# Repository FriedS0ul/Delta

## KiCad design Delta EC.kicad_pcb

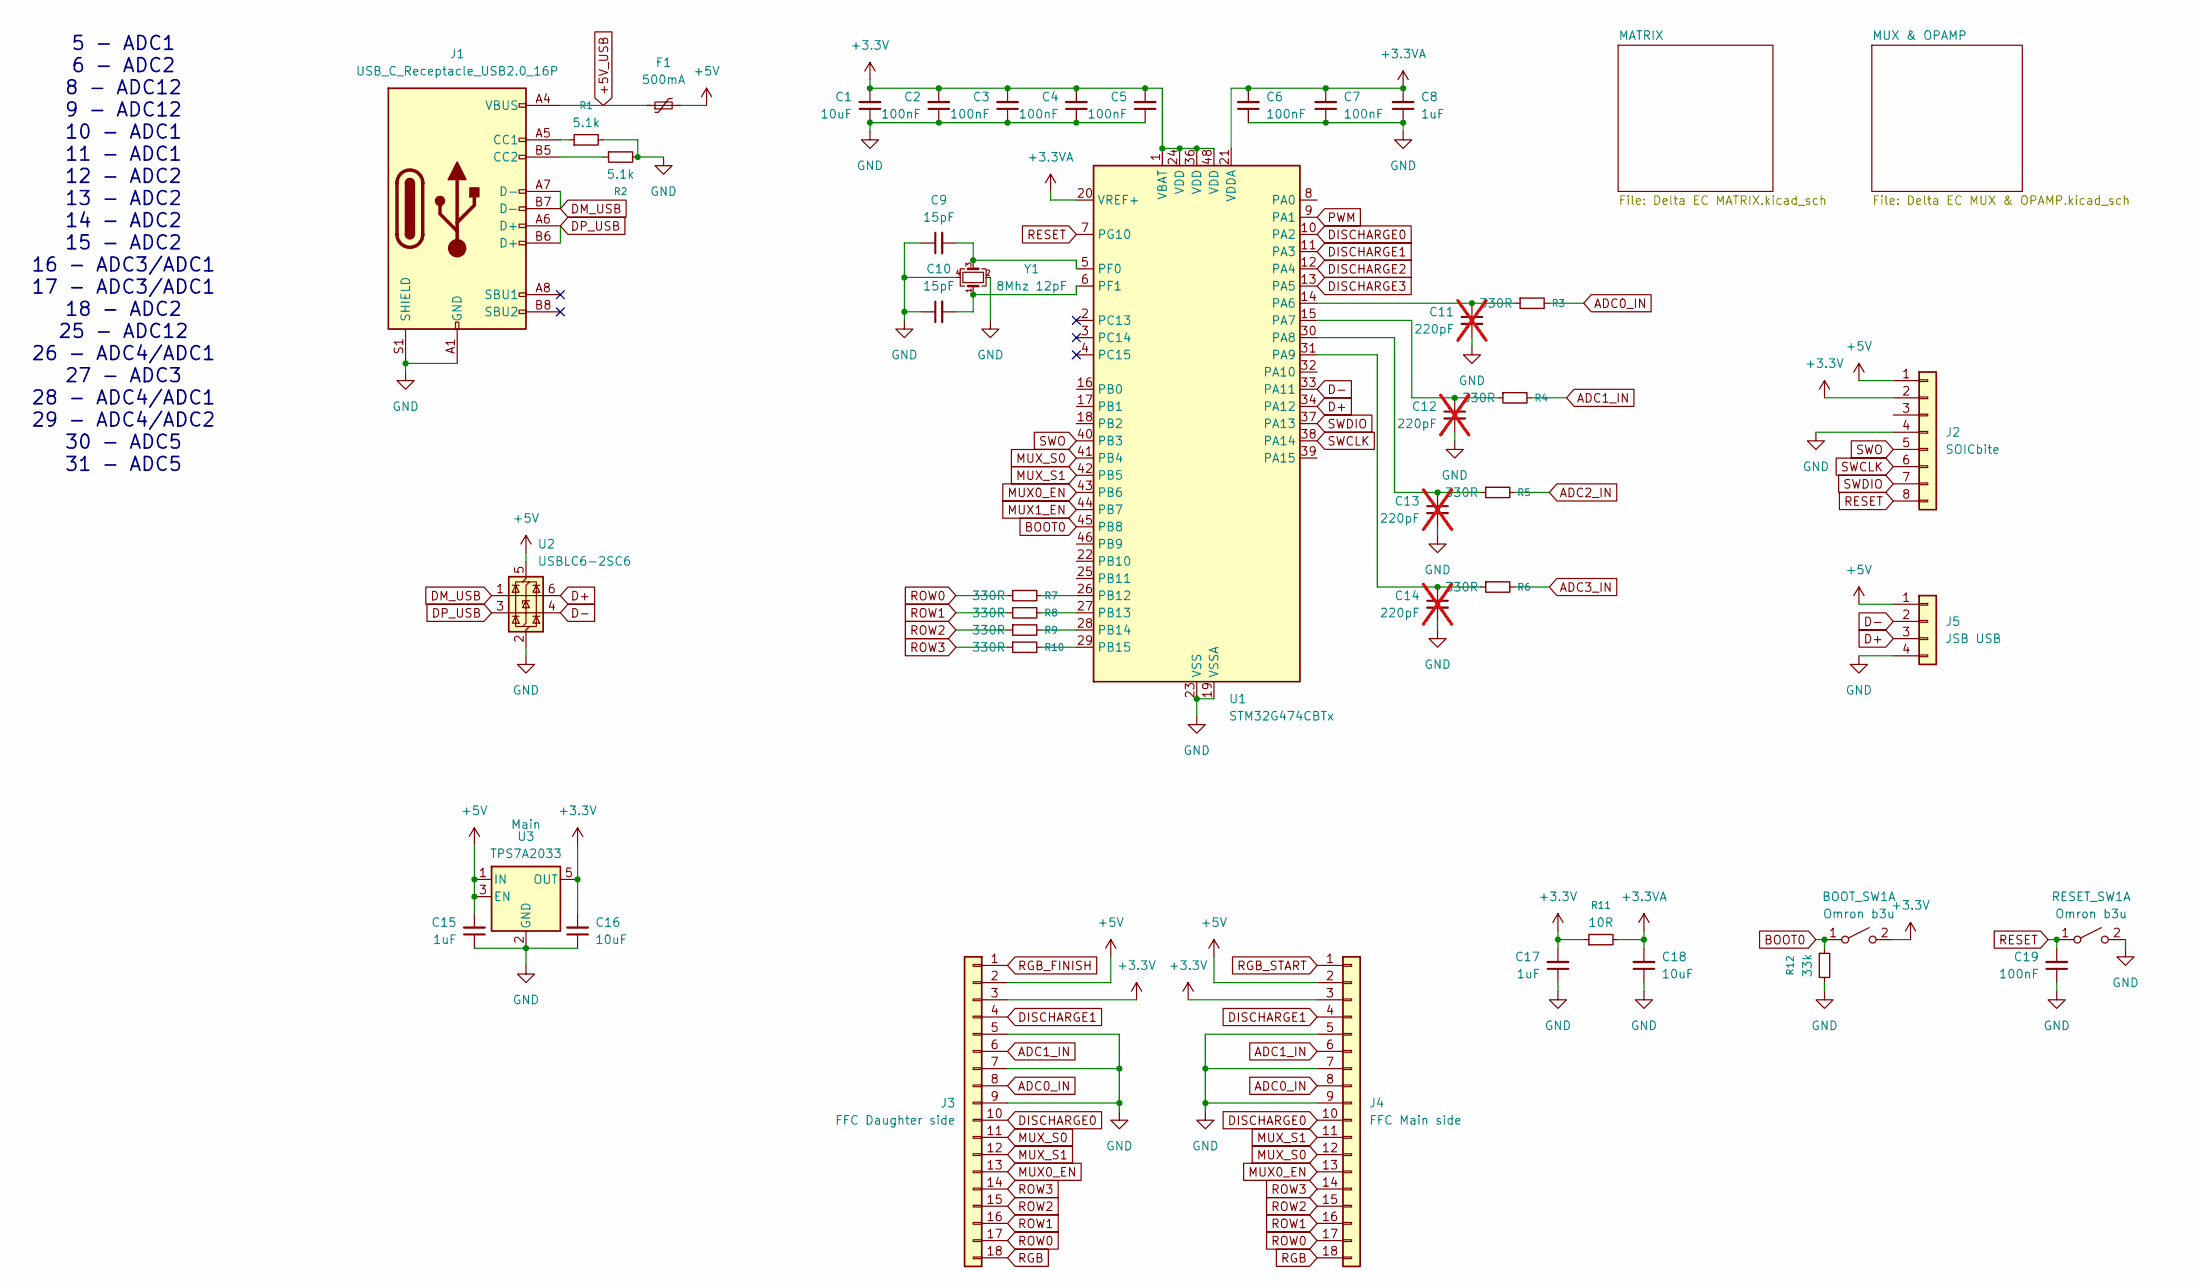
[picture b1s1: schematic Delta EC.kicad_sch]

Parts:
BOOT_SW1: Omron b3u; SW_SPST_B3U-1000P
C1, C16, C18: 10uF; C_0805_2012Metric
C2, C3, C4, C5, C6, C7, C19: 100nF; C_0402_1005Metric
C8, C15, C17: 1uF; C_0603_1608Metric
C9, C10: 15pF; C_0402_1005Metric
C11, C12, C13, C14: 220pF; C_0603_1608Metric; not fitted
F1: 500mA; Fuse_1206_3216Metric
J1: USB_C_Receptacle_USB2.0_16P; USB_C_Receptacle_GCT_USB4105-xx-A_16P_TopMnt_Horizontal
J2: SOICbite; SOICbite_footprint
J3: FFC Daughter side; TE_1-1734839-8_1x18-1MP_P0.5mm_Horizontal
J4: FFC Main side; TE_1-1734839-8_1x18-1MP_P0.5mm_Horizontal
J5: JSB USB; JST_SH_SM04B-SRSS-TB_1x04-1MP_P1.00mm_Horizontal
R1, R2: 5.1k; R_0603_1608Metric
R3, R4, R5, R6, R7, R8, R9, R10: 330R; R_0603_1608Metric
R11: 10R; R_0603_1608Metric
R12: 33k; R_0603_1608Metric
RESET_SW1: Omron b3u; SW_SPST_B3U-1000P
U1: STM32G474CBTx; LQFP-48_7x7mm_P0.5mm
U2: USBLC6-2SC6; SOT-23-6
U3: TPS7A2033; SOT-23-5
Y1: 8Mhz 12pF; Crystal_SMD_3225-4Pin_3.2x2.5mm

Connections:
+3.3V: BOOT_SW1.2 (B), C1.2, C2.2, C3.2, C4.2, C5.2, C16.2, C17.2, J2.2, J3.3, J4.3, R11.1, U1.1 (VBAT), U1.24 (VDD), U1.36 (VDD), U1.48 (VDD), U3.5 (OUT)
+3.3VA: C6.2, C7.2, C8.2, C18.2, R11.2, U1.20 (VREF+), U1.21 (VDDA); also elsewhere on the board
+5V: C15.2, F1.2, J2.1, J3.2, J4.2, J5.1, U2.5 (VBUS), U3.1 (IN), U3.3 (EN); also elsewhere on the board
+5V_USB: F1.1, J1.A4 (VBUS), J1.A9 (VBUS), J1.B4 (VBUS), J1.B9 (VBUS)
ADC0_IN: J3.8, J4.8, R3.2; also elsewhere on the board
ADC1_IN: J3.6, J4.6, R4.2; also elsewhere on the board
ADC2_IN: R5.2; also elsewhere on the board
ADC3_IN: R6.2; also elsewhere on the board
BOOT0: BOOT_SW1.1 (A), R12.1, U1.45 (PB8)
D+: J5.3, U1.34 (PA12), U2.6 (I/O1)
D-: J5.2, U1.33 (PA11), U2.4 (I/O2)
DISCHARGE0: J3.10, J4.10, U1.10 (PA2); also elsewhere on the board
DISCHARGE1: J3.4, J4.4, U1.11 (PA3); also elsewhere on the board
DISCHARGE2: U1.12 (PA4); also elsewhere on the board
DISCHARGE3: U1.13 (PA5); also elsewhere on the board
DM_USB: J1.A7 (D-), J1.B7 (D-), U2.1 (I/O1)
DP_USB: J1.A6 (D+), J1.B6 (D+), U2.3 (I/O2)
GND: C1.1, C2.1, C3.1, C4.1, C5.1, C6.1, C7.1, C8.1, C9.1, C10.1, C11.2, C12.2, C13.2, C14.2, C15.1, C16.1, C17.1, C18.1, C19.1, J1.A1 (GND), J1.A12 (GND), J1.B1 (GND), J1.B12 (GND), J1.S1 (SHIELD), J2.4, J3.5, J3.7, J3.9, J4.5, J4.7, J4.9, J5.4, R1.2, R2.2, R12.2, RESET_SW1.2 (B), U1.19 (VSSA), U1.23 (VSS), U1.35 (VSS), U1.47 (VSS), U2.2 (GND), U3.2 (GND), Y1.2, Y1.4; also elsewhere on the board
MUX0_EN: J3.13, J4.13, U1.43 (PB6); also elsewhere on the board
MUX1_EN: U1.44 (PB7); also elsewhere on the board
MUX_S0: J3.11, J4.12, U1.41 (PB4); also elsewhere on the board
MUX_S1: J3.12, J4.11, U1.42 (PB5); also elsewhere on the board
unnamed: J1.A5 (CC1), R1.1
unnamed: J1.B5 (CC2), R2.1
unnamed: C11.1, R3.1, U1.14 (PA6)
unnamed: C12.1, R4.1, U1.15 (PA7)
unnamed: C13.1, R5.1, U1.30 (PA8)
unnamed: C14.1, R6.1, U1.31 (PA9)
unnamed: R7.2, U1.26 (PB12)
unnamed: R8.2, U1.27 (PB13)
unnamed: R9.2, U1.28 (PB14)
unnamed: R10.2, U1.29 (PB15)
unnamed: C9.2, U1.5 (PF0), Y1.3
unnamed: C10.2, U1.6 (PF1), Y1.1
PWM: U1.9 (PA1)
RESET: C19.2, J2.8, RESET_SW1.1 (A), U1.7 (PG10)
RGB: J3.18, J4.18; also elsewhere on the board
RGB_FINISH: J3.1; also elsewhere on the board
RGB_START: J4.1; also elsewhere on the board
ROW0: J3.17, J4.17, R7.1; also elsewhere on the board
ROW1: J3.16, J4.16, R8.1; also elsewhere on the board
ROW2: J3.15, J4.15, R9.1; also elsewhere on the board
ROW3: J3.14, J4.14, R10.1; also elsewhere on the board
SWCLK: J2.6, U1.38 (PA14)
SWDIO: J2.7, U1.37 (PA13)
SWO: J2.5, U1.40 (PB3)

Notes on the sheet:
5 - ADC1 6 - ADC2 8 - ADC12 9 - ADC12 10 - ADC1 11 - ADC1 12 - ADC2 13 - ADC2 14 - ADC2 15 - ADC2 16 - ADC3/ADC1 17 - ADC3/ADC1 18 - ADC2 25 - ADC12 26 - ADC4/ADC1 27 - ADC3 28 - ADC4/ADC1 29 - ADC4/ADC2 30 - ADC5 31 - ADC5

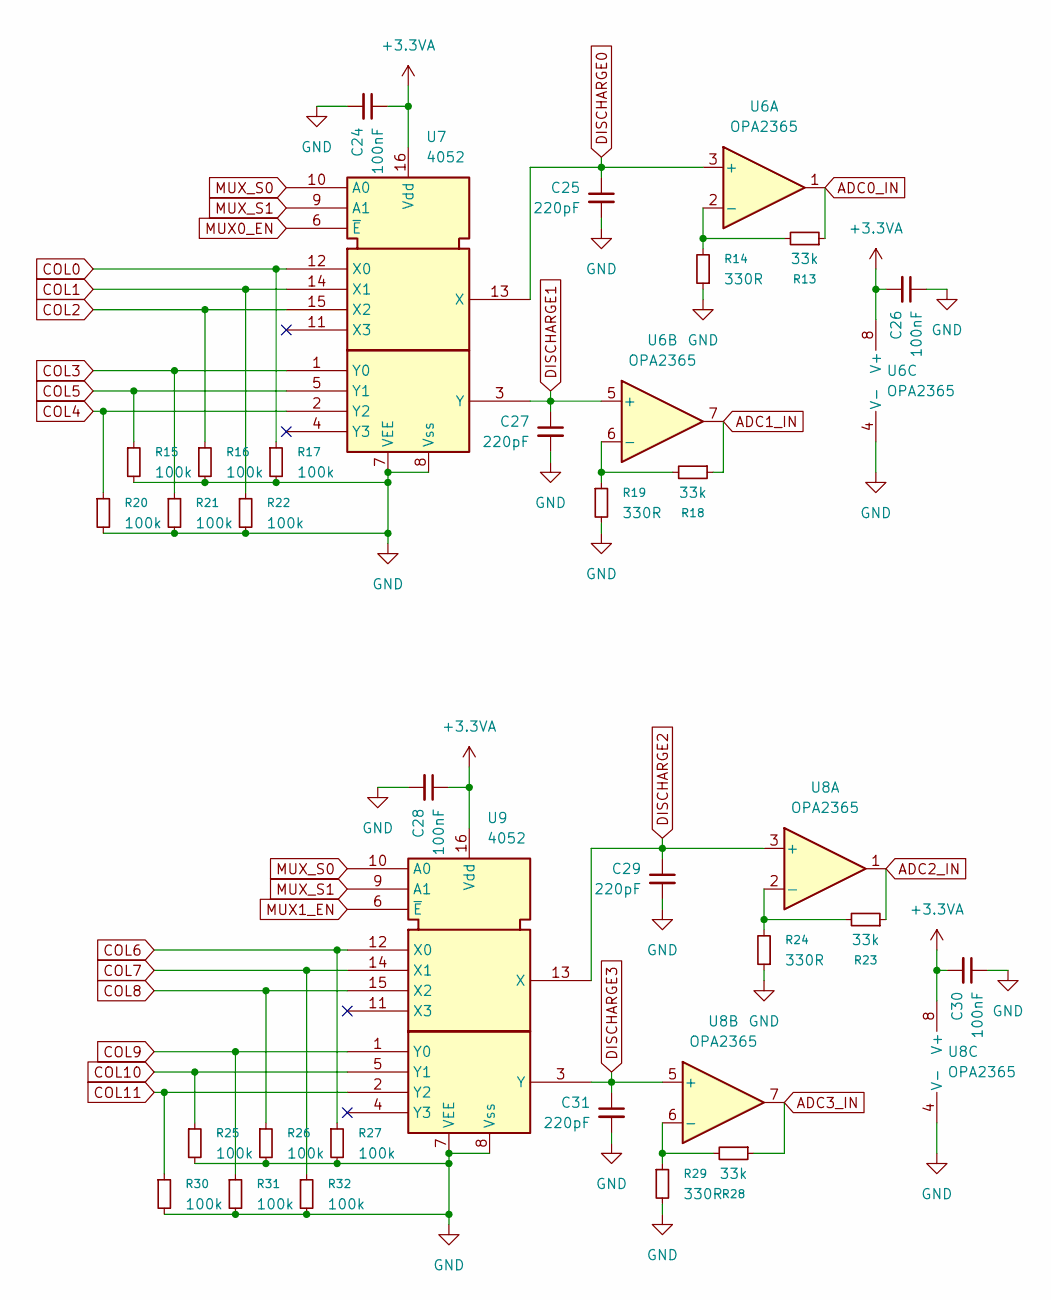
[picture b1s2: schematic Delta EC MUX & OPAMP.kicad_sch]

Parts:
C24, C26, C28, C30: 100nF; C_0402_1005Metric
C25, C27, C29, C31: 220pF; C_0603_1608Metric
R13, R18, R23, R28: 33k; R_0603_1608Metric
R14, R19, R24, R29: 330R; R_0603_1608Metric
R15, R16, R17, R20, R21, R22, R25, R26, R27, R30, R31, R32: 100k; R_0805_2012Metric
U6, U8: OPA2365; SOIC-8_3.9x4.9mm_P1.27mm
U7, U9: 4052; TSSOP-16_4.4x5mm_P0.65mm

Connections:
+3.3VA: C24.1, C26.2, C28.1, C30.2, U6.8 (V+), U7.16 (Vdd), U8.8 (V+), U9.16 (Vdd); also elsewhere on the board
ADC0_IN: R13.1, U6.1; also elsewhere on the board
ADC1_IN: R18.1, U6.7; also elsewhere on the board
ADC2_IN: R23.1, U8.1; also elsewhere on the board
ADC3_IN: R28.1, U8.7; also elsewhere on the board
COL0: R17.1, U7.12 (X0); also elsewhere on the board
COL1: R22.1, U7.14 (X1); also elsewhere on the board
COL2: R16.1, U7.15 (X2); also elsewhere on the board
COL3: R21.1, U7.1 (Y0); also elsewhere on the board
COL4: R20.1, U7.2 (Y2); also elsewhere on the board
COL5: R15.1, U7.5 (Y1); also elsewhere on the board
COL6: R27.1, U9.12 (X0); also elsewhere on the board
COL7: R32.1, U9.14 (X1); also elsewhere on the board
COL8: R26.1, U9.15 (X2); also elsewhere on the board
COL9: R31.1, U9.1 (Y0); also elsewhere on the board
COL10: R25.1, U9.5 (Y1); also elsewhere on the board
COL11: R30.1, U9.2 (Y2); also elsewhere on the board
DISCHARGE0: C25.1, U6.3 (+), U7.13 (X); also elsewhere on the board
DISCHARGE1: C27.1, U6.5 (+), U7.3 (Y); also elsewhere on the board
DISCHARGE2: C29.1, U8.3 (+), U9.13 (X); also elsewhere on the board
DISCHARGE3: C31.1, U8.5 (+), U9.3 (Y); also elsewhere on the board
GND: C24.2, C25.2, C26.1, C27.2, C28.2, C29.2, C30.1, C31.2, R14.1, R15.2, R16.2, R17.2, R19.2, R20.2, R21.2, R22.2, R24.1, R25.2, R26.2, R27.2, R29.2, R30.2, R31.2, R32.2, U6.4 (V-), U7.7 (VEE), U7.8 (Vss), U8.4 (V-), U9.7 (VEE), U9.8 (Vss); also elsewhere on the board
MUX0_EN: U7.6 (~E); also elsewhere on the board
MUX1_EN: U9.6 (~E); also elsewhere on the board
MUX_S0: U7.10 (A0), U9.10 (A0); also elsewhere on the board
MUX_S1: U7.9 (A1), U9.9 (A1); also elsewhere on the board
unnamed: R13.2, R14.2, U6.2 (-)
unnamed: R18.2, R19.1, U6.6 (-)
unnamed: R23.2, R24.2, U8.2 (-)
unnamed: R28.2, R29.1, U8.6 (-)

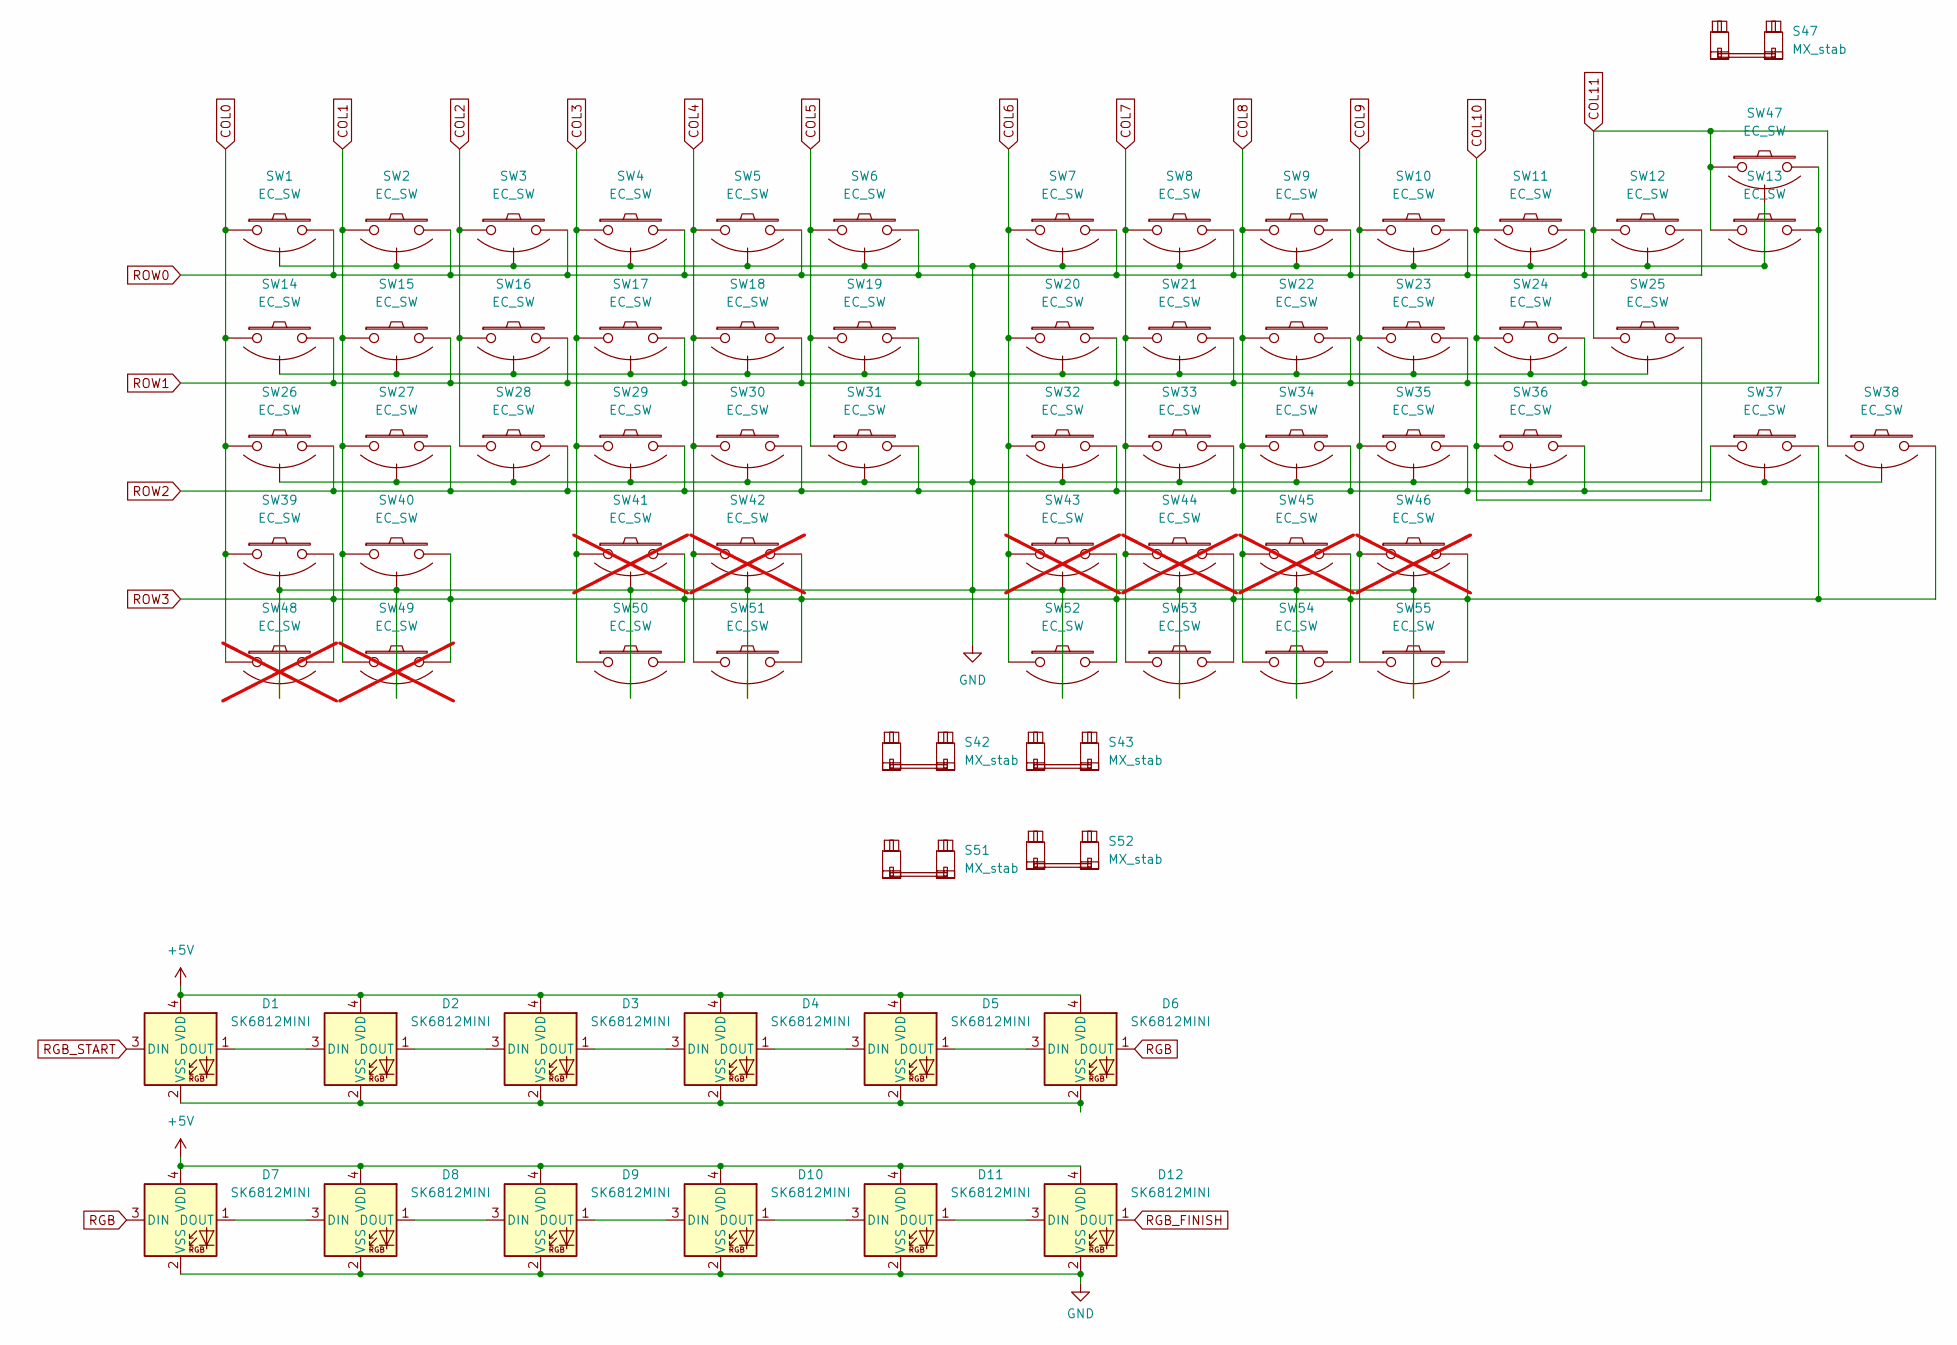
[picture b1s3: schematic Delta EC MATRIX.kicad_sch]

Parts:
D1, D2, D3, D4, D5, D6, D7, D8, D9, D10, D11, D12: SK6812MINI; LED_SK6812MINI_PLCC4_3.5x3.5mm_P1.75mm
S42, S47, S52: MX_stab; STAB_MX_2u
S43, S51: MX_stab; STAB_MX_2.25u
SW1, SW2, SW3, SW4, SW5, SW6, SW7, SW8, SW9, SW10, SW11, SW12, SW13, SW14, SW15, SW16, SW17, SW18, SW19, SW20, SW21, SW22, SW23, SW24, SW26, SW27, SW28, SW29, SW30, SW31, SW37, SW38, SW47: EC_SW; ecs_pad_1U_hybrid_hotswap_V3
SW25, SW32, SW33, SW34, SW35, SW36: EC_SW; ecs_pad_1U_hybrid_hotswap_V3_switched_sides
SW39, SW40, SW50, SW51, SW52, SW53, SW54, SW55: EC_SW; ecs_pad_hybrid_hotswap_2.381_V3
SW41, SW42, SW43, SW44, SW45, SW46, SW48, SW49: EC_SW; ecs_pad_1U_hybrid_hotswap_V2; not fitted

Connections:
+5V: D1.4 (VDD), D2.4 (VDD), D3.4 (VDD), D4.4 (VDD), D5.4 (VDD), D6.4 (VDD), D7.4 (VDD), D8.4 (VDD), D9.4 (VDD), D10.4 (VDD), D11.4 (VDD), D12.4 (VDD); also elsewhere on the board
COL0: SW1.1, SW14.1, SW26.1, SW39.1, SW48.1; also elsewhere on the board
COL1: SW2.1, SW15.1, SW27.1, SW40.1, SW49.1; also elsewhere on the board
COL2: SW3.1, SW16.1, SW28.1; also elsewhere on the board
COL3: SW4.1, SW17.1, SW29.1, SW41.1, SW50.1; also elsewhere on the board
COL4: SW5.1, SW18.1, SW30.1, SW42.1, SW51.1; also elsewhere on the board
COL5: SW6.1, SW19.1, SW31.1; also elsewhere on the board
COL6: SW7.1, SW20.1, SW32.1, SW43.1, SW52.1; also elsewhere on the board
COL7: SW8.1, SW21.1, SW33.1, SW44.1, SW53.1; also elsewhere on the board
COL8: SW9.1, SW22.1, SW34.1, SW45.1, SW54.1; also elsewhere on the board
COL9: SW10.1, SW23.1, SW35.1, SW46.1, SW55.1; also elsewhere on the board
COL10: SW11.1, SW24.1, SW36.1, SW37.1; also elsewhere on the board
COL11: SW12.1, SW13.1, SW25.1, SW38.1, SW47.1; also elsewhere on the board
GND: D7.2 (VSS), D8.2 (VSS), D9.2 (VSS), D10.2 (VSS), D11.2 (VSS), D12.2 (VSS), SW1.3 (SG), SW2.3 (SG), SW3.3 (SG), SW4.3 (SG), SW5.3 (SG), SW6.3 (SG), SW7.3 (SG), SW8.3 (SG), SW9.3 (SG), SW10.3 (SG), SW11.3 (SG), SW12.3 (SG), SW13.3 (SG), SW14.3 (SG), SW15.3 (SG), SW16.3 (SG), SW17.3 (SG), SW18.3 (SG), SW19.3 (SG), SW20.3 (SG), SW21.3 (SG), SW22.3 (SG), SW23.3 (SG), SW24.3 (SG), SW25.3 (SG), SW26.3 (SG), SW27.3 (SG), SW28.3 (SG), SW29.3 (SG), SW30.3 (SG), SW31.3 (SG), SW32.3 (SG), SW33.3 (SG), SW34.3 (SG), SW35.3 (SG), SW36.3 (SG), SW37.3 (SG), SW38.3 (SG), SW39.3 (SG), SW40.3 (SG), SW41.3 (SG), SW42.3 (SG), SW43.3 (SG), SW44.3 (SG), SW45.3 (SG), SW46.3 (SG), SW47.3 (SG), SW48.3 (SG), SW49.3 (SG), SW50.3 (SG), SW51.3 (SG), SW52.3 (SG), SW53.3 (SG), SW54.3 (SG), SW55.3 (SG); also elsewhere on the board
unnamed: D1.1 (DOUT), D2.3 (DIN)
unnamed: D1.2 (VSS), D2.2 (VSS), D3.2 (VSS), D4.2 (VSS), D5.2 (VSS), D6.2 (VSS)
unnamed: D2.1 (DOUT), D3.3 (DIN)
unnamed: D3.1 (DOUT), D4.3 (DIN)
unnamed: D4.1 (DOUT), D5.3 (DIN)
unnamed: D5.1 (DOUT), D6.3 (DIN)
unnamed: D7.1 (DOUT), D8.3 (DIN)
unnamed: D8.1 (DOUT), D9.3 (DIN)
unnamed: D9.1 (DOUT), D10.3 (DIN)
unnamed: D10.1 (DOUT), D11.3 (DIN)
unnamed: D11.1 (DOUT), D12.3 (DIN)
RGB: D6.1 (DOUT), D7.3 (DIN); also elsewhere on the board
RGB_FINISH: D12.1 (DOUT); also elsewhere on the board
RGB_START: D1.3 (DIN); also elsewhere on the board
ROW0: SW1.2, SW2.2, SW3.2, SW4.2, SW5.2, SW6.2, SW7.2, SW8.2, SW9.2, SW10.2, SW11.2, SW12.2; also elsewhere on the board
ROW1: SW13.2, SW14.2, SW15.2, SW16.2, SW17.2, SW18.2, SW19.2, SW20.2, SW21.2, SW22.2, SW23.2, SW24.2, SW47.2; also elsewhere on the board
ROW2: SW25.2, SW26.2, SW27.2, SW28.2, SW29.2, SW30.2, SW31.2, SW32.2, SW33.2, SW34.2, SW35.2, SW36.2; also elsewhere on the board
ROW3: SW37.2, SW38.2, SW39.2, SW40.2, SW41.2, SW42.2, SW43.2, SW44.2, SW45.2, SW46.2, SW48.2, SW49.2, SW50.2, SW51.2, SW52.2, SW53.2, SW54.2, SW55.2; also elsewhere on the board

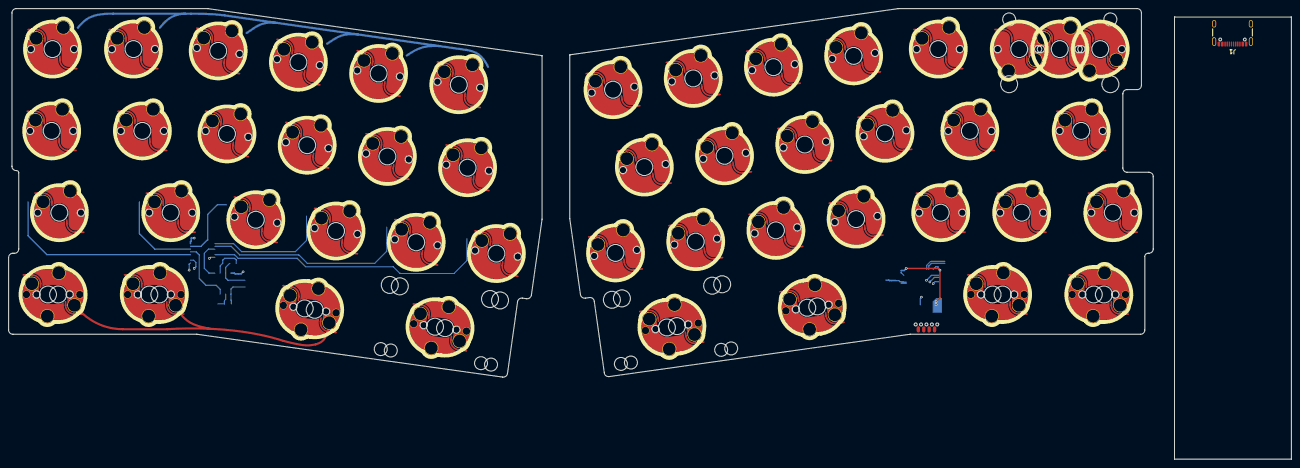
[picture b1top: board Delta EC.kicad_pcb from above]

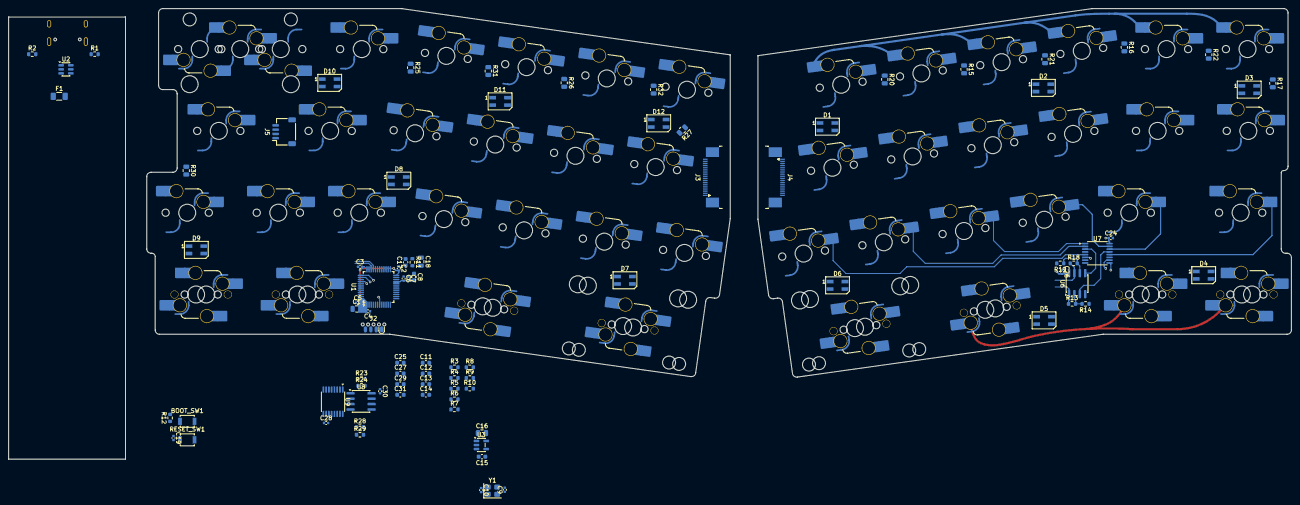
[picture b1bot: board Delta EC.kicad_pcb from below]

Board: 2 copper layers, 301.7 x 106.0 mm, 139 parts (86 on the bottom side), 72 nets.

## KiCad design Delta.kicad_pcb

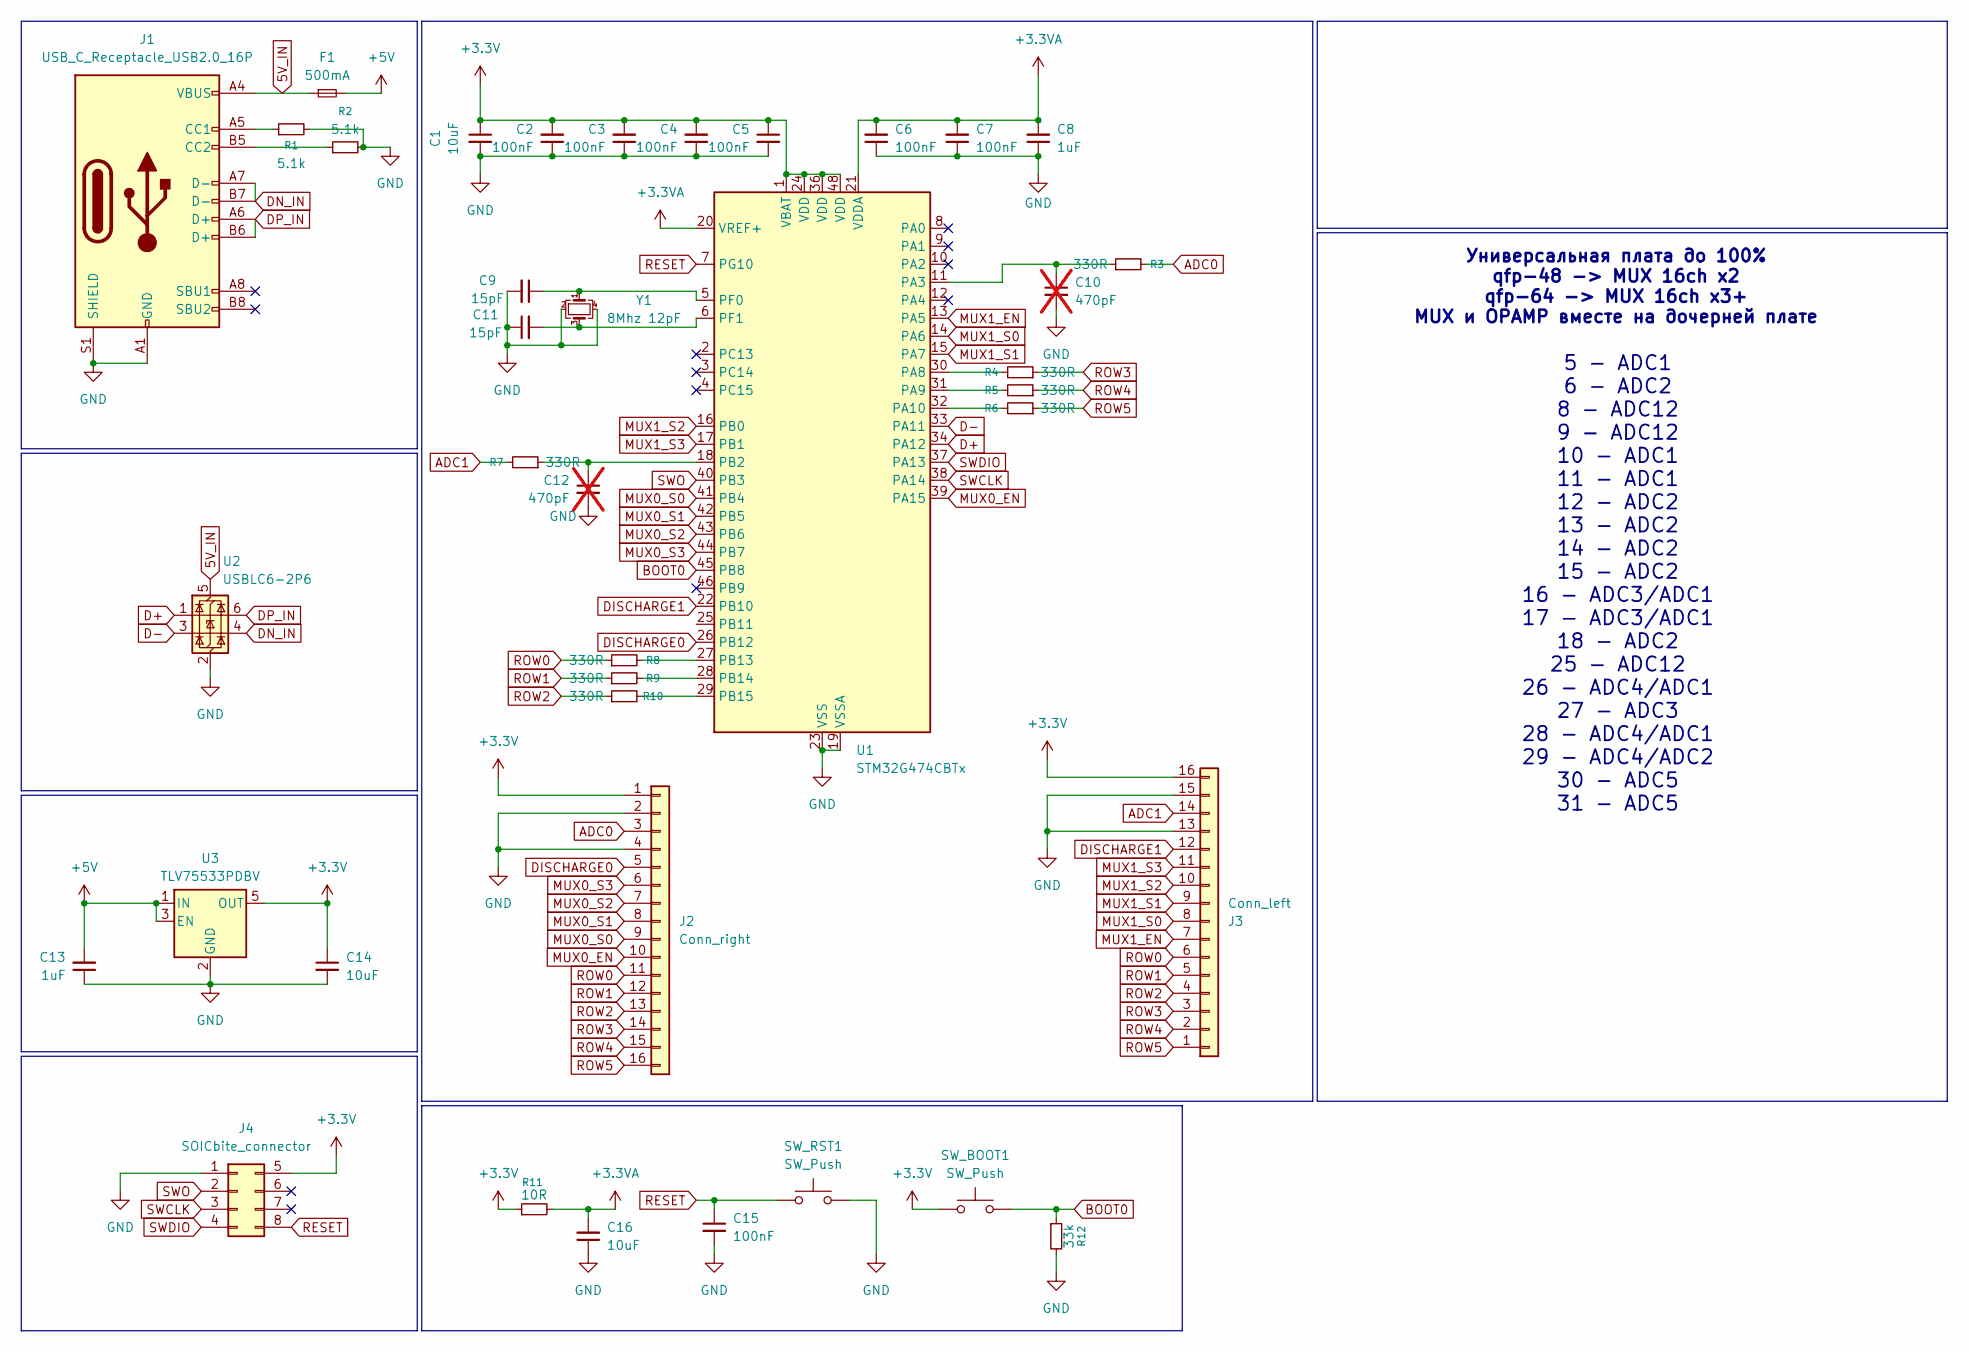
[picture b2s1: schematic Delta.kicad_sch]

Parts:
C1, C14, C16: 10uF; C_0805_2012Metric
C2, C3, C4, C5, C6, C7, C15: 100nF; C_0402_1005Metric
C8, C13: 1uF; C_0603_1608Metric
C9, C11: 15pF; C_0402_1005Metric
C10, C12: 470pF; C_0603_1608Metric; not fitted
F1: 500mA; Fuse_1206_3216Metric
J1: USB_C_Receptacle_USB2.0_16P; USB_C_Receptacle_G-Switch_GT-USB-7010ASV
J2: Conn_right; TE_1-84953-6_1x16-1MP_P1.0mm_Horizontal
J3: Conn_left; TE_1-84953-6_1x16-1MP_P1.0mm_Horizontal
J4: SOICbite_connector; SOIC_clipProgSmall
R1, R2: 5.1k; R_0603_1608Metric
R3, R4, R5, R6, R7, R8, R9, R10: 330R; R_0603_1608Metric
R11: 10R; R_0603_1608Metric
R12: 33k; R_0603_1608Metric
SW_BOOT1: SW_Push; SW_SPST_B3U-1000P
SW_RST1: SW_Push; SW_SPST_B3U-1000P
U1: STM32G474CBTx; LQFP-48_7x7mm_P0.5mm
U2: USBLC6-2P6; SOT-23-6
U3: TLV75533PDBV; SOT-23-5
Y1: 8Mhz 12pF; Crystal_SMD_3225-4Pin_3.2x2.5mm

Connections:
5V_IN: F1.1, J1.A4 (VBUS), J1.A9 (VBUS), J1.B4 (VBUS), J1.B9 (VBUS), U2.5 (VBUS)
+3.3V: C1.1, C2.2, C3.2, C4.2, C5.1, C14.1, J2.1, J3.16, J4.5, R11.1, SW_BOOT1.1, U1.1 (VBAT), U1.24 (VDD), U1.36 (VDD), U1.48 (VDD), U3.5 (OUT)
+3.3VA: C6.2, C7.2, C8.2, C16.2, R11.2, U1.20 (VREF+), U1.21 (VDDA)
+5V: C13.2, F1.2, U3.1 (IN), U3.3 (EN)
ADC0: J2.3, R3.2
ADC1: J3.14, R7.2
BOOT0: R12.1, SW_BOOT1.2, U1.45 (PB8)
D+: U1.34 (PA12), U2.1 (I/O1)
D-: U1.33 (PA11), U2.3 (I/O2)
DISCHARGE0: J2.5, U1.26 (PB12)
DISCHARGE1: J3.12, U1.22 (PB10)
DN_IN: J1.A7 (D-), J1.B7 (D-), U2.4 (I/O2)
DP_IN: J1.A6 (D+), J1.B6 (D+), U2.6 (I/O1)
GND: C1.2, C2.1, C3.1, C4.1, C5.2, C6.1, C7.1, C8.1, C9.2, C10.2, C11.1, C12.2, C13.1, C14.2, C15.2, C16.1, J1.A1 (GND), J1.A12 (GND), J1.B1 (GND), J1.B12 (GND), J1.S1 (SHIELD), J2.2, J2.4, J3.13, J3.15, J4.1, R1.2, R2.2, R12.2, SW_RST1.2, U1.19 (VSSA), U1.23 (VSS), U1.35 (VSS), U1.47 (VSS), U2.2 (GND), U3.2 (GND), Y1.2, Y1.4
MUX0_EN: J2.10, U1.39 (PA15)
MUX0_S0: J2.9, U1.41 (PB4)
MUX0_S1: J2.8, U1.42 (PB5)
MUX0_S2: J2.7, U1.43 (PB6)
MUX0_S3: J2.6, U1.44 (PB7)
MUX1_EN: J3.7, U1.13 (PA5)
MUX1_S0: J3.8, U1.14 (PA6)
MUX1_S1: J3.9, U1.15 (PA7)
MUX1_S2: J3.10, U1.16 (PB0)
MUX1_S3: J3.11, U1.17 (PB1)
unnamed: J1.A5 (CC1), R1.1
unnamed: J1.B5 (CC2), R2.1
unnamed: C10.1, R3.1, U1.11 (PA3)
unnamed: R4.2, U1.30 (PA8)
unnamed: R5.2, U1.31 (PA9)
unnamed: R6.2, U1.32 (PA10)
unnamed: C12.1, R7.1, U1.18 (PB2)
unnamed: R8.2, U1.27 (PB13)
unnamed: R9.2, U1.28 (PB14)
unnamed: R10.2, U1.29 (PB15)
unnamed: C9.1, U1.5 (PF0), Y1.1
unnamed: C11.2, U1.6 (PF1), Y1.3
RESET: C15.1, J4.8, SW_RST1.1, U1.7 (PG10)
ROW0: J2.11, J3.6, R8.1
ROW1: J2.12, J3.5, R9.1
ROW2: J2.13, J3.4, R10.1
ROW3: J2.14, J3.3, R4.1
ROW4: J2.15, J3.2, R5.1
ROW5: J2.16, J3.1, R6.1
SWCLK: J4.3, U1.38 (PA14)
SWDIO: J4.4, U1.37 (PA13)
SWO: J4.2, U1.40 (PB3)

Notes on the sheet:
Универсальная плата до 100% qfp-48 -> MUX 16ch x2 qfp-64 -> MUX 16ch x3+ MUX и OPAMP вместе на дочерней плате
5 - ADC1 6 - ADC2 8 - ADC12 9 - ADC12 10 - ADC1 11 - ADC1 12 - ADC2 13 - ADC2 14 - ADC2 15 - ADC2 16 - ADC3/ADC1 17 - ADC3/ADC1 18 - ADC2 25 - ADC12 26 - ADC4/ADC1 27 - ADC3 28 - ADC4/ADC1 29 - ADC4/ADC2 30 - ADC5 31 - ADC5

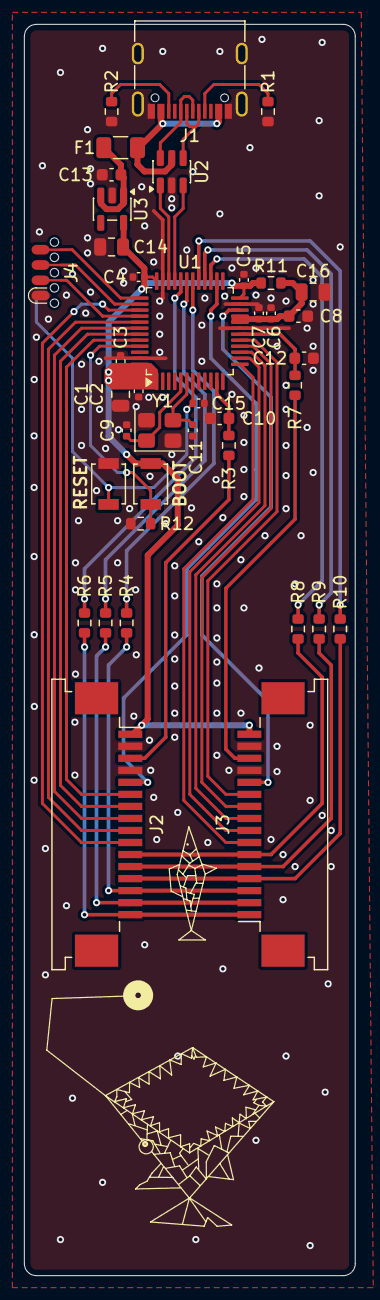
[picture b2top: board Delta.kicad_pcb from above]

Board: 2 copper layers, 27.5 x 104.0 mm, 39 parts (0 on the bottom side), 46 nets.

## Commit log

2026-04-08 08.04.2026
2026-04-08 09.04.2026
2026-04-10 10.04.2026
2026-04-12 12.04.2026
2026-04-13 13.04.2026
2026-04-14 14.04.2026
2026-04-16 16.04.2026
2026-04-17 17.04.2026
2026-05-12 12.05.2026
